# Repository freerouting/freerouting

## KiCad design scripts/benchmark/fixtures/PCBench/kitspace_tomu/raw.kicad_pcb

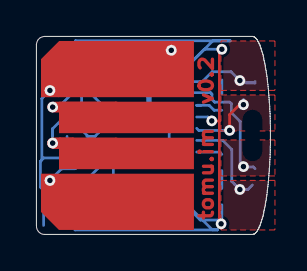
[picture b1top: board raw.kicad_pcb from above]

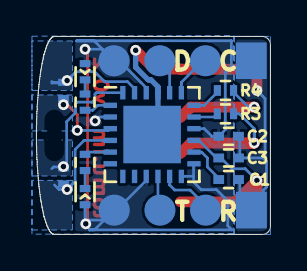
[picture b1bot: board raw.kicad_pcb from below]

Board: 2 copper layers, 13.0 x 11.0 mm, 15 parts (14 on the bottom side), 20 nets.

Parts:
C1, C2: 1uF; C_0402
C3: 47uF; C_0402
D1, D2: LED; LED_0402
P1: USART0; debug-points
P2: DEBUG; debug-points
P3: USB-PCB
R1, R2: 75; R_0402
R3, R4: 15; R_0402
U1: EFM32HG309; QFN-24-1EP_5x5mm_Pitch0.65mm
W1: CAP0; minimal-points
W2: CAP1; minimal-points

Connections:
+3V3: C2.1, D1.2, D2.2, P1.4, P2.4, U1.2, U1.9, U1.12, U1.13, U1.16, U1.22
/CAP0A: U1.3, W1.2
/CAP0B: U1.23, W1.1
/CAP1A: U1.4, W2.2
/CAP1B: U1.24, W2.1
/DBG_SWCLK: P2.2, U1.19
/DBG_SWDIO: P2.3, U1.20
/DEC: C1.2, U1.14
/LED0: R2.2, U1.5
/LED1: R1.1, U1.1
/LEU0_RX: P1.2, U1.11
/LEU0_TX: P1.3, U1.10
/RUSB_D+: R4.2, U1.18
/RUSB_D-: R3.2, U1.17
/USB_5V: C3.1, P3.1, U1.15
/USB_D+: P3.3, R4.1
/USB_D-: P3.2, R3.1
GND: C1.1, C2.2, C3.2, P1.1, P2.1, P3.4, U1.21, U1.25
unnamed: D1.1, R1.2
unnamed: D2.1, R2.1

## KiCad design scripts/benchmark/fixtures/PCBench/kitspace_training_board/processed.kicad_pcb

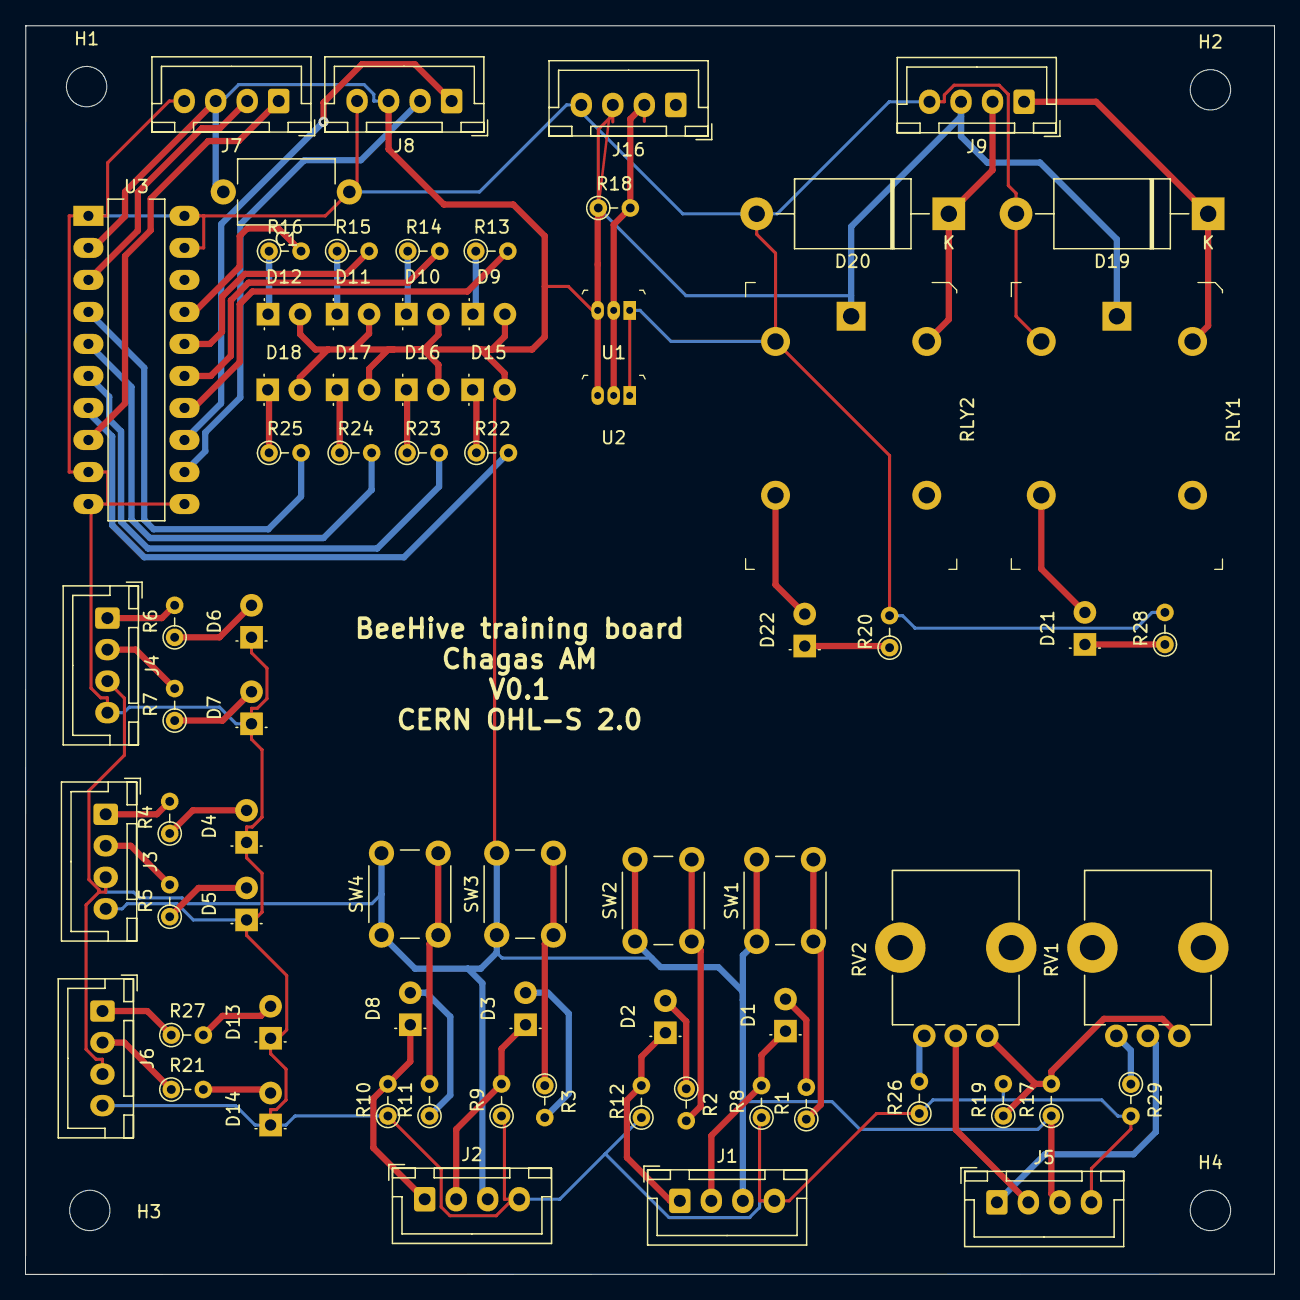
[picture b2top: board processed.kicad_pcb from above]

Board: 2 copper layers, 99.1 x 99.1 mm, 77 parts (0 on the bottom side), 58 nets.

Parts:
C1: 100nf; C_Disc_D7.5mm_W5.0mm_P10.00mm
D1, D2, D3, D4, D5, D6, D7, D8, D9, D10, D11, D12, D13, D14, D15, D16, D17, D18, D21, D22: LED; LED_D3.0mm
D19, D20: D_Schottky; D_DO-201AE_P15.24mm_Horizontal
H1, H2, H3, H4: MountingHole; MountingHole_3.2mm_M3_DIN965
J1, J2, J3, J4, J5, J6, J7, J8, J9, J16: Conn_01x04; JST_XH_B4B-XH-A_1x04_P2.50mm_Vertical
R1, R2, R3, R4, R5, R6, R7, R11, R17: 220; R_Axial_DIN0204_L3.6mm_D1.6mm_P2.54mm_Vertical
R8, R9, R10, R12: 1k; R_Axial_DIN0204_L3.6mm_D1.6mm_P2.54mm_Vertical
R13, R14, R15, R16, R20, R21, R22, R23, R24, R25, R27, R28: 560; R_Axial_DIN0204_L3.6mm_D1.6mm_P2.54mm_Vertical
R18: 4.7k; R_Axial_DIN0204_L3.6mm_D1.6mm_P2.54mm_Vertical
R19, R26, R29: 330; R_Axial_DIN0204_L3.6mm_D1.6mm_P2.54mm_Vertical
RLY1, RLY2: G5LE-14_DC5; Relay_THT_G5LE-14
RV1, RV2: 1k; Potentiometer_Alps_RK09K_Single_Vertical
SW1, SW2, SW3, SW4: SW_Push; SW_PUSH_6mm
U1, U2: DS18S20_; TO-92-3
U3: TPIC6595; DIP-20_W7.62mm_LongPads

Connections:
+5V: C1.2, D9.2, D10.2, D11.2, D12.2, D15.2, D16.2, D17.2, D18.2, J1.3, J2.3, J3.3, J4.3, J5.3, J6.3, J7.3, J8.3, J9.3, J16.3, R17.1, R18.1, RLY1.1, RLY2.1, SW1.1, SW2.1, SW3.1, SW4.1, U1.3, U2.3, U3.2
GND: C1.1, D4.1, D5.1, D6.1, D7.1, D13.1, D14.1, D19.2, D20.2, J1.4, J2.4, J3.4, J4.4, J5.4, J6.4, J7.4, J8.4, J9.4, J16.4, R8.1, R9.1, R10.1, R12.1, R19.2, R20.2, R26.1, R28.2, R29.2, RLY1.2, RLY2.2, U1.1, U2.1, U3.1, U3.9, U3.10, U3.11, U3.19, U3.20
unnamed: D1.1, J1.2, R8.2
unnamed: D1.2, R1.2
unnamed: D2.1, J1.1, R12.2
unnamed: D2.2, R2.1
unnamed: D3.1, J2.2, R9.2
unnamed: D3.2, R3.2
unnamed: D4.2, R4.1
unnamed: D5.2, R5.1
unnamed: D6.2, R6.1
unnamed: D7.2, R7.1
unnamed: D8.1, J2.1, R10.2
unnamed: D8.2, R11.1
unnamed: D9.1, R13.1
unnamed: D10.1, R14.1
unnamed: D11.1, R15.1
unnamed: D12.1, R16.1
unnamed: D13.2, R27.2
unnamed: D14.2, R21.2
unnamed: D15.1, R22.1
unnamed: D16.1, R23.1
unnamed: D17.1, R24.1
unnamed: D18.1, R25.1
unnamed: D19.1, J9.1, RLY1.5
unnamed: D20.1, J9.2, RLY2.5
unnamed: D21.1, R28.1
unnamed: D21.2, RLY1.3
unnamed: D22.1, R20.1
unnamed: D22.2, RLY2.3
unnamed: J3.1, R4.2
unnamed: J3.2, R5.2
unnamed: J4.1, R6.2
unnamed: J4.2, R7.2
unnamed: J5.1, RV1.2
unnamed: J5.2, RV2.2
unnamed: J6.1, R27.1
unnamed: J6.2, R21.1
unnamed: J7.1, U3.8
unnamed: J7.2, U3.3
unnamed: J8.1, U3.13
unnamed: J8.2, U3.12
unnamed: J16.2, R18.2, U1.2, U2.2
unnamed: R1.1, SW1.2
unnamed: R2.2, SW2.2
unnamed: R3.1, SW3.2
unnamed: R11.2, SW4.2
unnamed: R13.2, U3.14
unnamed: R14.2, U3.15
unnamed: R15.2, U3.16
unnamed: R16.2, U3.17
unnamed: R17.2, R19.1, RV1.1, RV2.1
unnamed: R22.2, U3.7
unnamed: R23.2, U3.6
unnamed: R24.2, U3.5
unnamed: R25.2, U3.4
unnamed: R26.2, RV2.3
unnamed: R29.1, RV1.3

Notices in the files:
scripts/benchmark/fixtures/PCBench/kitspace_tomu/raw.kicad_pcb:
License: CC-BY-SA 4.0 or TAPR
scripts/benchmark/fixtures/PCBench/kitspace_training_board/processed.kicad_pcb:
CERN OHL-S 2.0
